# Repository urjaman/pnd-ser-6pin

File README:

TTL UART w/ flow control from the pandora ext port
--------------------------------------------------

Parts list:
- 1* 74LVC14AD SO-14 "Hex inverting Schmitt trigger with 5 V tolerant input"
- 1* 0.1u 0603 cap
- 2* NX3008NBKW,115 SOT-323 n-ch mosfet
- 2* 4k7 4x0603 resistor arrays
- pandora ext port connector

The PCB is shared at oshpark:
https://oshpark.com/shared_projects/iGVFJWpa
remember to pick the 0.8mm service

This takes out the UART2 (not the debug UART but the one with flow control)
of the pandora ext port into the familiar 6-pin 0.1" header (*)
and converts it to 2.8V levels and provides the ext port power as the VCC.

Inputs are 5V tolerant so you can ignore the VCC and interface with 
CMOS devices running at 2.8 - 4.2V. 2.8V might be out-of-spec as a one
for 5V CMOS devices but it will not harm the device if you try anyways.
It should be fine for 5V TTL devices.

(* N.B. the 6th pin is RTS and not DTR as you might've hoped, but you might
be able to workaround this in software if you want that... )

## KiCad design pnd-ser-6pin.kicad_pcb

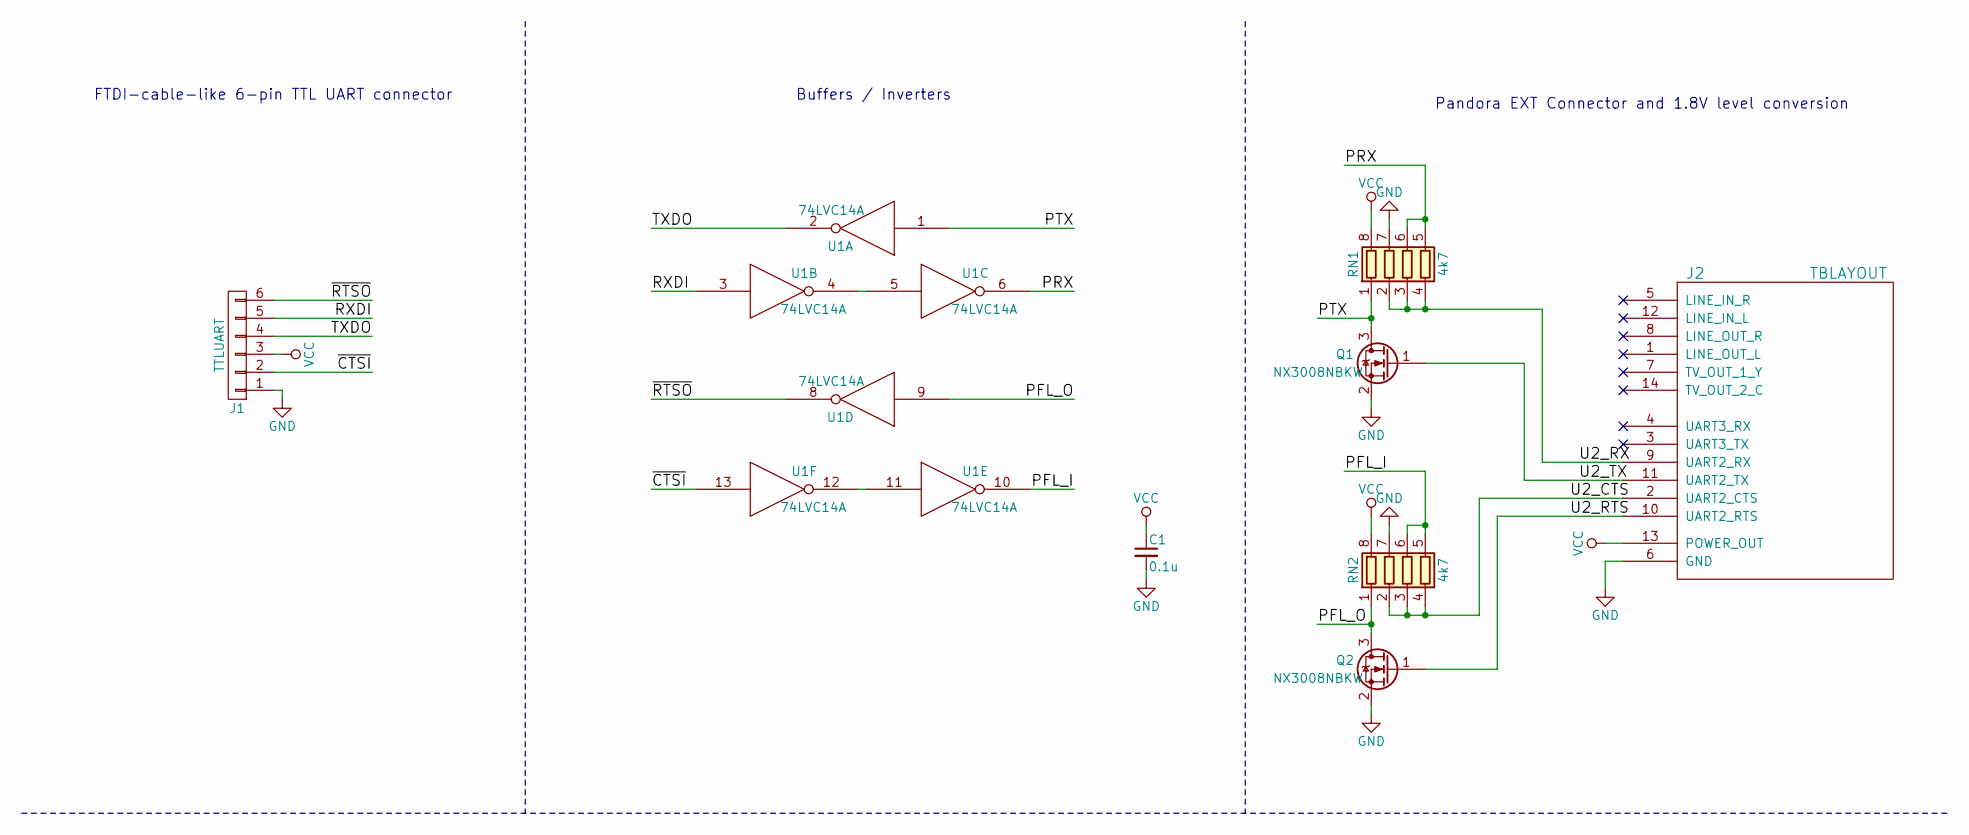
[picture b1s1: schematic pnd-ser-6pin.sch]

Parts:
C1: 0.1u; C_0603_HandSoldering
J1: TTLUART; Pin_Header_Angled_1x06_Pitch2.54mm
J2: TBLAYOUT; TBLAYOUT-ASTRON
Q1, Q2: NX3008NBKW; SOT-323_SC-70_Handsoldering
RN1, RN2: 4k7; R_Array_Convex_4x0603
U1: 74LVC14A; SOIC-14_3.9x8.7mm_Pitch1.27mm

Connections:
/PFL_I: RN2.5 (R4.2), RN2.6 (R3.2), U1.10
/PFL_O: Q2.3 (D), RN2.1 (R1.1), U1.9
/PRX: RN1.5 (R4.2), RN1.6 (R3.2), U1.6
/PTX: Q1.3 (D), RN1.1 (R1.1), U1.1
/RXDI: J1.5, U1.3
/TXDO: J1.4, U1.2
/U2_CTS: J2.2 (UART2_CTS), RN2.2 (R2.1), RN2.3 (R3.1), RN2.4 (R4.1)
/U2_RTS: J2.10 (UART2_RTS), Q2.1 (G)
/U2_RX: J2.9 (UART2_RX), RN1.2 (R2.1), RN1.3 (R3.1), RN1.4 (R4.1)
/U2_TX: J2.11 (UART2_TX), Q1.1 (G)
/~CTSI: J1.2, U1.13
/~RTSO: J1.6, U1.8
GND: C1.2, J1.1, J2.6 (GND), Q1.2 (S), Q2.2 (S), RN1.7 (R2.2), RN2.7 (R2.2), U1.7 (GND)
unnamed: U1.4, U1.5
unnamed: U1.11, U1.12
VCC: C1.1, J1.3, J2.13 (POWER_OUT), RN1.8 (R1.2), RN2.8 (R1.2), U1.14 (VCC)

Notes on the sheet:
Pandora EXT Connector and 1.8V level conversion
Buffers / Inverters
FTDI-cable-like 6-pin TTL UART connector

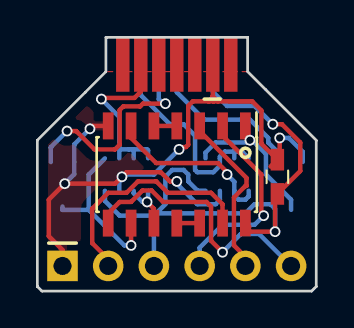
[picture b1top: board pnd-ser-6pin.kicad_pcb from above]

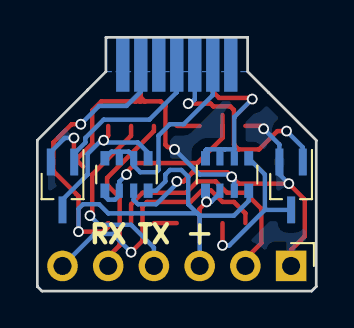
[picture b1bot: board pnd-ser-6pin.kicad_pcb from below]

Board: 2 copper layers, 15.5 x 14.1 mm, 8 parts (6 on the bottom side), 16 nets.

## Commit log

2017-07-30 Initial project
